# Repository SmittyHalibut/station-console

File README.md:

# station-console
A station console, to connect an operator, logger, and radio together

This branch (v1-eagle) is the first version I made of the console.

**IT IS BROKEN!  DO NOT BUILD AS IT IS!!**

~Unfortunately, I can't remember what is broke, I built it 5 years ago.
So instead, I'll describe what the INTENTION was, and let you figure it out.~

**I REMEMBER!** When connected to power, it would brown out the supply and draw
as much current as possible. I just debugged it and figured out that I wired the
2.1mm barrel plug backwards!  Oops.  So I'm going to remove the barrel plugs, 
solder wires in their place, and put Anderson Powerpoles at the end of the wire.

# Goals:
* Allow an operator and a logger to both have headsets on and use an HF radio.
* Audio outputs are mixed, with individual volume knobs for each input:
  * Audio into the mic port on the radio is mixed from the operator and loggers's mics.
  * Audio into the operator and loggers headsets is mixed from eachothers' mics,
    and the speaker audio from the radio.
  * Audio into the external speaker is from the speaker audio from the radio.
* All inputs have a simple VU meter (two LEDs) to set input levels.  
* Audio connections to the radio are transformer isolated, so no ground loops.
* Audio connections to the head sets and external speaker are on the console ground,
  which is tied to power ground.
* PTT is not handled by this mixer console at all. PTT must be routed externally.

# Build:
These files are from an old version of Eagle, circa 2015.  I don't use Eagle anymore,
so I can't update the files.  You're on your own for any conversions.

You might be able to fabricate the board as it is and wire your own power in, leaving
off the 2.1mm barrel plug.

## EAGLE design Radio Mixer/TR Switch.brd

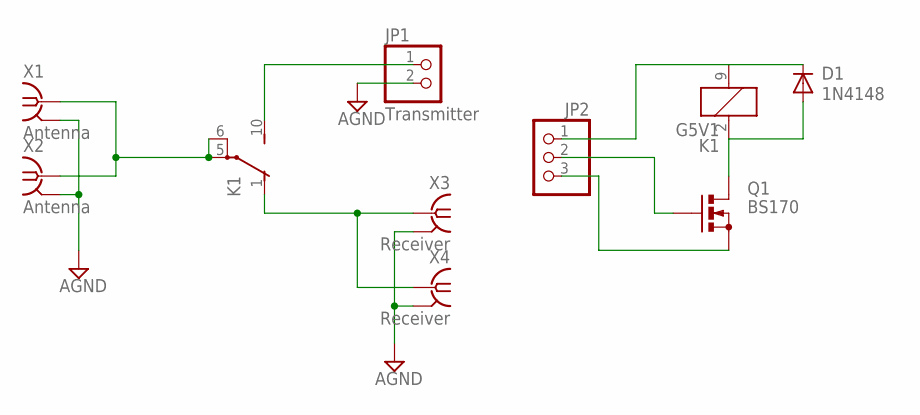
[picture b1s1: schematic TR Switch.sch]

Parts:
D1: 1N4148; DO35-7
JP1: Transmitter; 1X02
JP2: PINHD-1X3; 1X03
K1: G5V1
Q1: BS170; SOT54E
X1: Antenna; J502-ND-142-0711-821/826
X2: Antenna; BU-SMA-V
X3: Receiver; J502-ND-142-0711-821/826
X4: Receiver; BU-SMA-V

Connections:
AGND: JP1.2, X1.G@1 (2), X1.G@2 (2), X1.G@3 (2), X1.G@4 (2), X2.2, X2.3 (2), X2.4 (2), X2.5 (2), X3.G@1 (2), X3.G@2 (2), X3.G@3 (2), X3.G@4 (2), X4.2, X4.3 (2), X4.4 (2), X4.5 (2)
unnamed: D1.A, K1.2 (1), Q1.D
unnamed: D1.C, JP2.1, K1.9 (2)
unnamed: K1.5, K1.6, X1.1, X2.1
unnamed: JP2.3, Q1.S
unnamed: JP1.1, K1.10 (S)
unnamed: K1.1 (O), X3.1, X4.1
unnamed: JP2.2, Q1.G

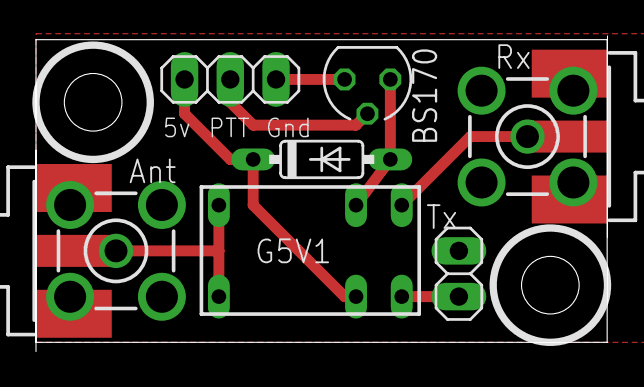
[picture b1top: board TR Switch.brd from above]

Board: 2 copper layers, 31.8 x 17.5 mm, 9 parts (0 on the bottom side), 8 nets.

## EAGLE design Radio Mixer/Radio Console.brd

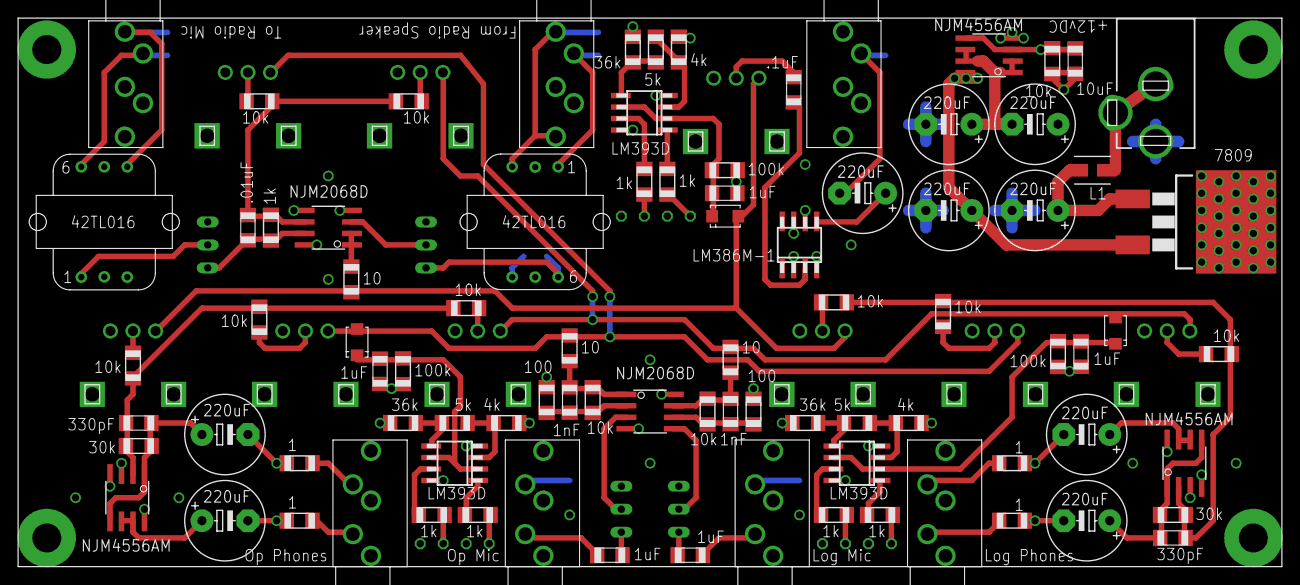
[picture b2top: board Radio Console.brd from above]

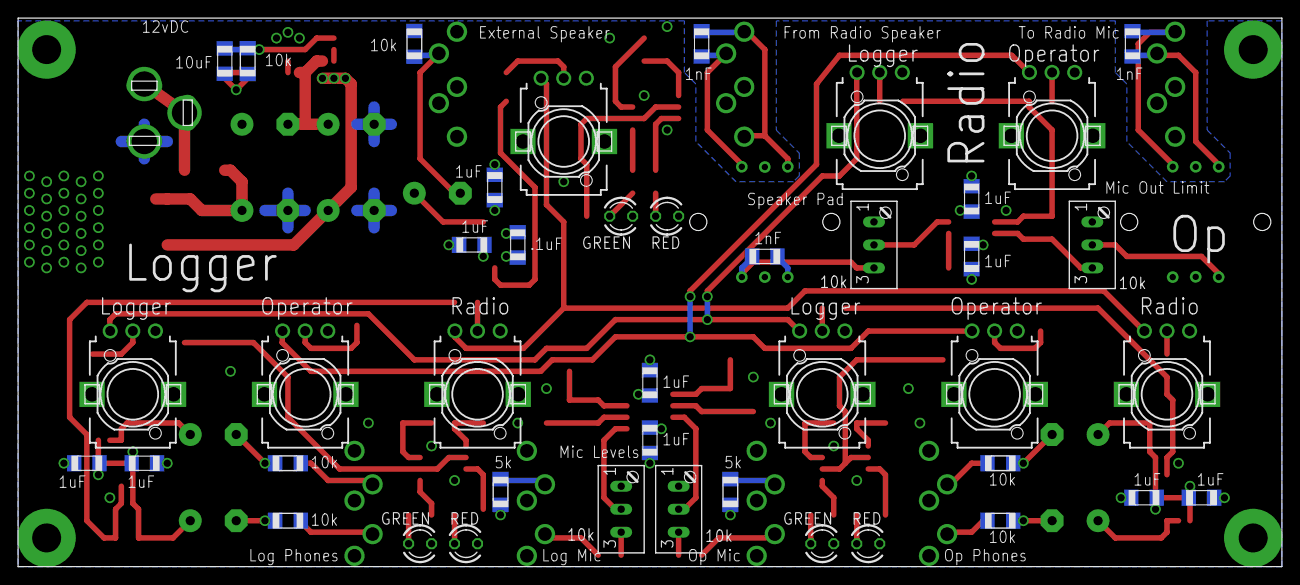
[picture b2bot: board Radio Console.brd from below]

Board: 4 copper layers, 139.7 x 60.6 mm, 128 parts (42 on the bottom side), 79 nets.

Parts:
C1, C12, C13, C14, C15, C16, C20, C21, C22, C23, C28, C30, C33, C34, C35: 1uF; C1206
C2, C3, C24, C31, C32: 1nF; C1206
C4, C5, C8, C11, C17, C18, C25, C26, C27: 220uF; E5-8,5
C6, C19: 330pF; C1206
C7: .01uF; C1206
C9, C10: 10uF; C1206
C29, C36: .1uF; C1206
IC1, IC2, IC3: NJM4556AM; SO08
IC4, IC5: NJM2068D; SO08
IC6, IC7, IC8: LM393D; SO08
IC10: LM386M-1; SO08
J1, J8: Operator Headphones; SJ1-353
J2: Operator Microphone; SJ1-353
J3: To Radio MIcrophone; SJ1-353
J4: Logger Headphone; SJ1-353
J5: Logger Microphone; SJ1-353
J6: From Radio Speaker Out; SJ1-353
J7: DCJ0303
L1: L4035M
LED1, LED3, LED5: GREEN; LED3MM
LED2, LED4, LED6: RED; LED3MM
R1, R28, R49, R57, R63: 5k; R1206
R2, R29, R32, R40: 10k; S64W
R3, R7, R9, R11, R15, R16, R18, R20, R22, R26, R27, R30, R36, R38, R41, R42, R44: 10k; R1206
R4, R31: 100; R1206
R5, R33, R34: 10; R1206
R6, R8, R10, R17, R19, R21, R35, R37, R50: EVU-F2AF30D14; EVUFXM
R12, R13, R23, R24: 1; R1206
R14, R25: 30k; R1206
R39, R54, R55, R60, R61, R66, R67: 1k; R1206
R48, R56, R62: 4k; R1206
R51, R58, R64: 36k; R1206
R53, R59, R65: 100k; R1206
TR1, TR2: 42TL016; 42TL
U1: 7809; D2PACK
U$1, U$2, U$3: RS07; DO-219AB

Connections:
GND: C8.-, C10.2, C11.-, C13.2, C15.2, C21.2, C23.2, C25.-, C30.2, C36.2, IC1.4, IC2.4, IC3.4, IC4.4, IC5.4, IC6.4, IC7.4, IC8.4, IC10.2, IC10.4, J1.P$1, J2.P$1, J2.P$4, J4.P$1, J5.P$1, J5.P$4, J7.1, J8.P$1, LED1.K, LED2.K, LED3.K, LED4.K, LED5.K, LED6.K, R15.1, R16.1, R26.1, R27.1, R42.1, R44.1, U1.2
LOG-LOUT: J4.P$2, R23.2
LOG-MICRING: J5.P$3, R1.1
LOG-MICTIP: C1.1, J5.P$2
LOG-ROUT: J4.P$3, R24.2
LOGBUS: R5.2, R8.3, R19.3, R37.3, U$3.ANODE
unnamed: C1.2, R2.E
unnamed: IC4.5, R2.S
unnamed: C3.1, IC4.6, R3.1, R4.2
unnamed: C3.2, IC4.7, R3.2, R5.1
unnamed: C2.1, R32.E, TR1.6
unnamed: R6.2, R7.1
unnamed: R8.2, R9.1
unnamed: R10.2, R11.1
unnamed: C17.-, R12.1, R26.2
unnamed: C18.-, R13.1, R27.2
unnamed: C6.2, IC3.2, R14.1, R18.2, R20.2, R22.2
unnamed: C19.2, IC2.2, R7.2, R9.2, R11.2, R25.1
unnamed: R17.2, R18.1
unnamed: R19.2, R20.1
unnamed: C20.2, R29.E
unnamed: R21.2, R22.1
unnamed: C4.-, R15.2, R23.1
unnamed: C5.-, R16.2, R24.1
unnamed: IC5.3, R32.S
unnamed: IC5.1, IC5.2, R33.1
unnamed: C7.2, IC5.6, R36.2, R38.2, R39.1
unnamed: R35.2, R36.1
unnamed: R37.2, R38.1
unnamed: C24.1, IC4.2, R30.1, R31.2
unnamed: C24.2, IC4.1, R30.2, R34.1
unnamed: C9.2, C10.1, IC1.3, IC1.5, R41.1, R42.2
unnamed: C29.2, IC10.3
unnamed: C36.1, IC10.7
unnamed: C29.1, R50.2
unnamed: C8.+, L1.2, U1.1
unnamed: C4.+, C6.1, IC3.1, IC3.5, R14.2
unnamed: C17.+, C19.1, IC2.1, IC2.5, R25.2
unnamed: C18.+, IC2.6, IC2.7
unnamed: C5.+, IC3.6, IC3.7
unnamed: IC4.3, R29.S
unnamed: C27.+, IC10.5
unnamed: R40.S, TR2.1
unnamed: C7.1, IC5.7, R39.2, R40.E
unnamed: IC6.3, R48.1, R49.2
unnamed: IC6.5, R49.1, R51.2
unnamed: C33.1, IC6.2, IC6.6, R53.2, U$1.CATHODE
unnamed: IC6.1, R54.1
unnamed: IC6.7, R55.1
unnamed: LED1.A, R54.2
unnamed: LED2.A, R55.2
unnamed: IC7.3, R56.1, R57.2
unnamed: IC7.5, R57.1, R58.2
unnamed: C34.1, IC7.2, IC7.6, R59.2, U$2.CATHODE
unnamed: IC7.1, R60.1
unnamed: IC7.7, R61.1
unnamed: LED3.A, R60.2
unnamed: LED4.A, R61.2
unnamed: IC8.3, R62.1, R63.2
unnamed: IC8.5, R63.1, R64.2
unnamed: C35.1, IC8.2, IC8.6, R65.2, U$3.CATHODE
unnamed: IC8.1, R66.1
unnamed: IC8.7, R67.1
unnamed: LED5.A, R66.2
unnamed: LED6.A, R67.2
OP-LOUT: J1.P$2, R13.2
OP-MICRING: J2.P$3, R28.1
OP-MICTIP: C20.1, J2.P$2
OP-ROUT: J1.P$3, R12.2
OPBUS: R6.3, R17.3, R34.2, R35.3, U$1.ANODE
RADBUS: R10.3, R21.3, R33.2, R50.3, U$2.ANODE
RADIN+: C31.1, J6.P$2, TR1.1
RADIN-: C31.2, J6.P$1, J6.P$4, TR1.3
RADMIC+: C32.1, J3.P$2, TR2.6
RADMIC-: C32.2, J3.P$1, TR2.4
SPK-OUT: C27.-, J8.P$2, R44.2
VCC: C9.1, C11.+, C12.1, C14.1, C16.1, C22.1, C26.+, C28.1, IC1.8, IC2.8, IC3.8, IC4.8, IC5.8, IC6.8, IC7.8, IC8.8, IC10.6, R1.2, R28.2, R41.2, R51.1, R58.1, R64.1, U1.3
VCC/2: C2.2, C12.2, C13.1, C14.2, C15.1, C16.2, C21.1, C22.2, C23.1, C25.+, C26.-, C28.2, C30.1, C33.2, C34.2, C35.2, IC1.1, IC1.2, IC1.6, IC1.7, IC2.3, IC3.3, IC5.5, R2.A, R4.1, R6.1, R8.1, R10.1, R17.1, R19.1, R21.1, R29.A, R31.1, R32.A, R35.1, R37.1, R40.A, R48.2, R50.1, R53.1, R56.2, R59.1, R62.2, R65.1, TR1.4, TR2.3
VIN: J7.2, J7.3, L1.1

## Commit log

2019-11-27 v1.0 as built in 2015. THIS VERSION IS BROKEN! See README.md
2019-11-27 Update README with intentions for v2.
2019-11-28 Schematic: near exact copy of v1 schematic, but in KiCAD (vs Eagle), removed VU meters, fixed a few things.
2019-11-28 UserConsole is the start of a modular version of this project.
2019-11-28 PDF of the schematic as of 2019-11-28.
2019-11-29 Updated README.md once I remembered what was wrong with this board. It can be hacked around!
2019-11-30 Progress on the PCB.
2020-02-02 https://www.youtube.com/watch?v=d2vIKhrSCEs Split into separate pages. Added block diagram documentation. Started board layout.
